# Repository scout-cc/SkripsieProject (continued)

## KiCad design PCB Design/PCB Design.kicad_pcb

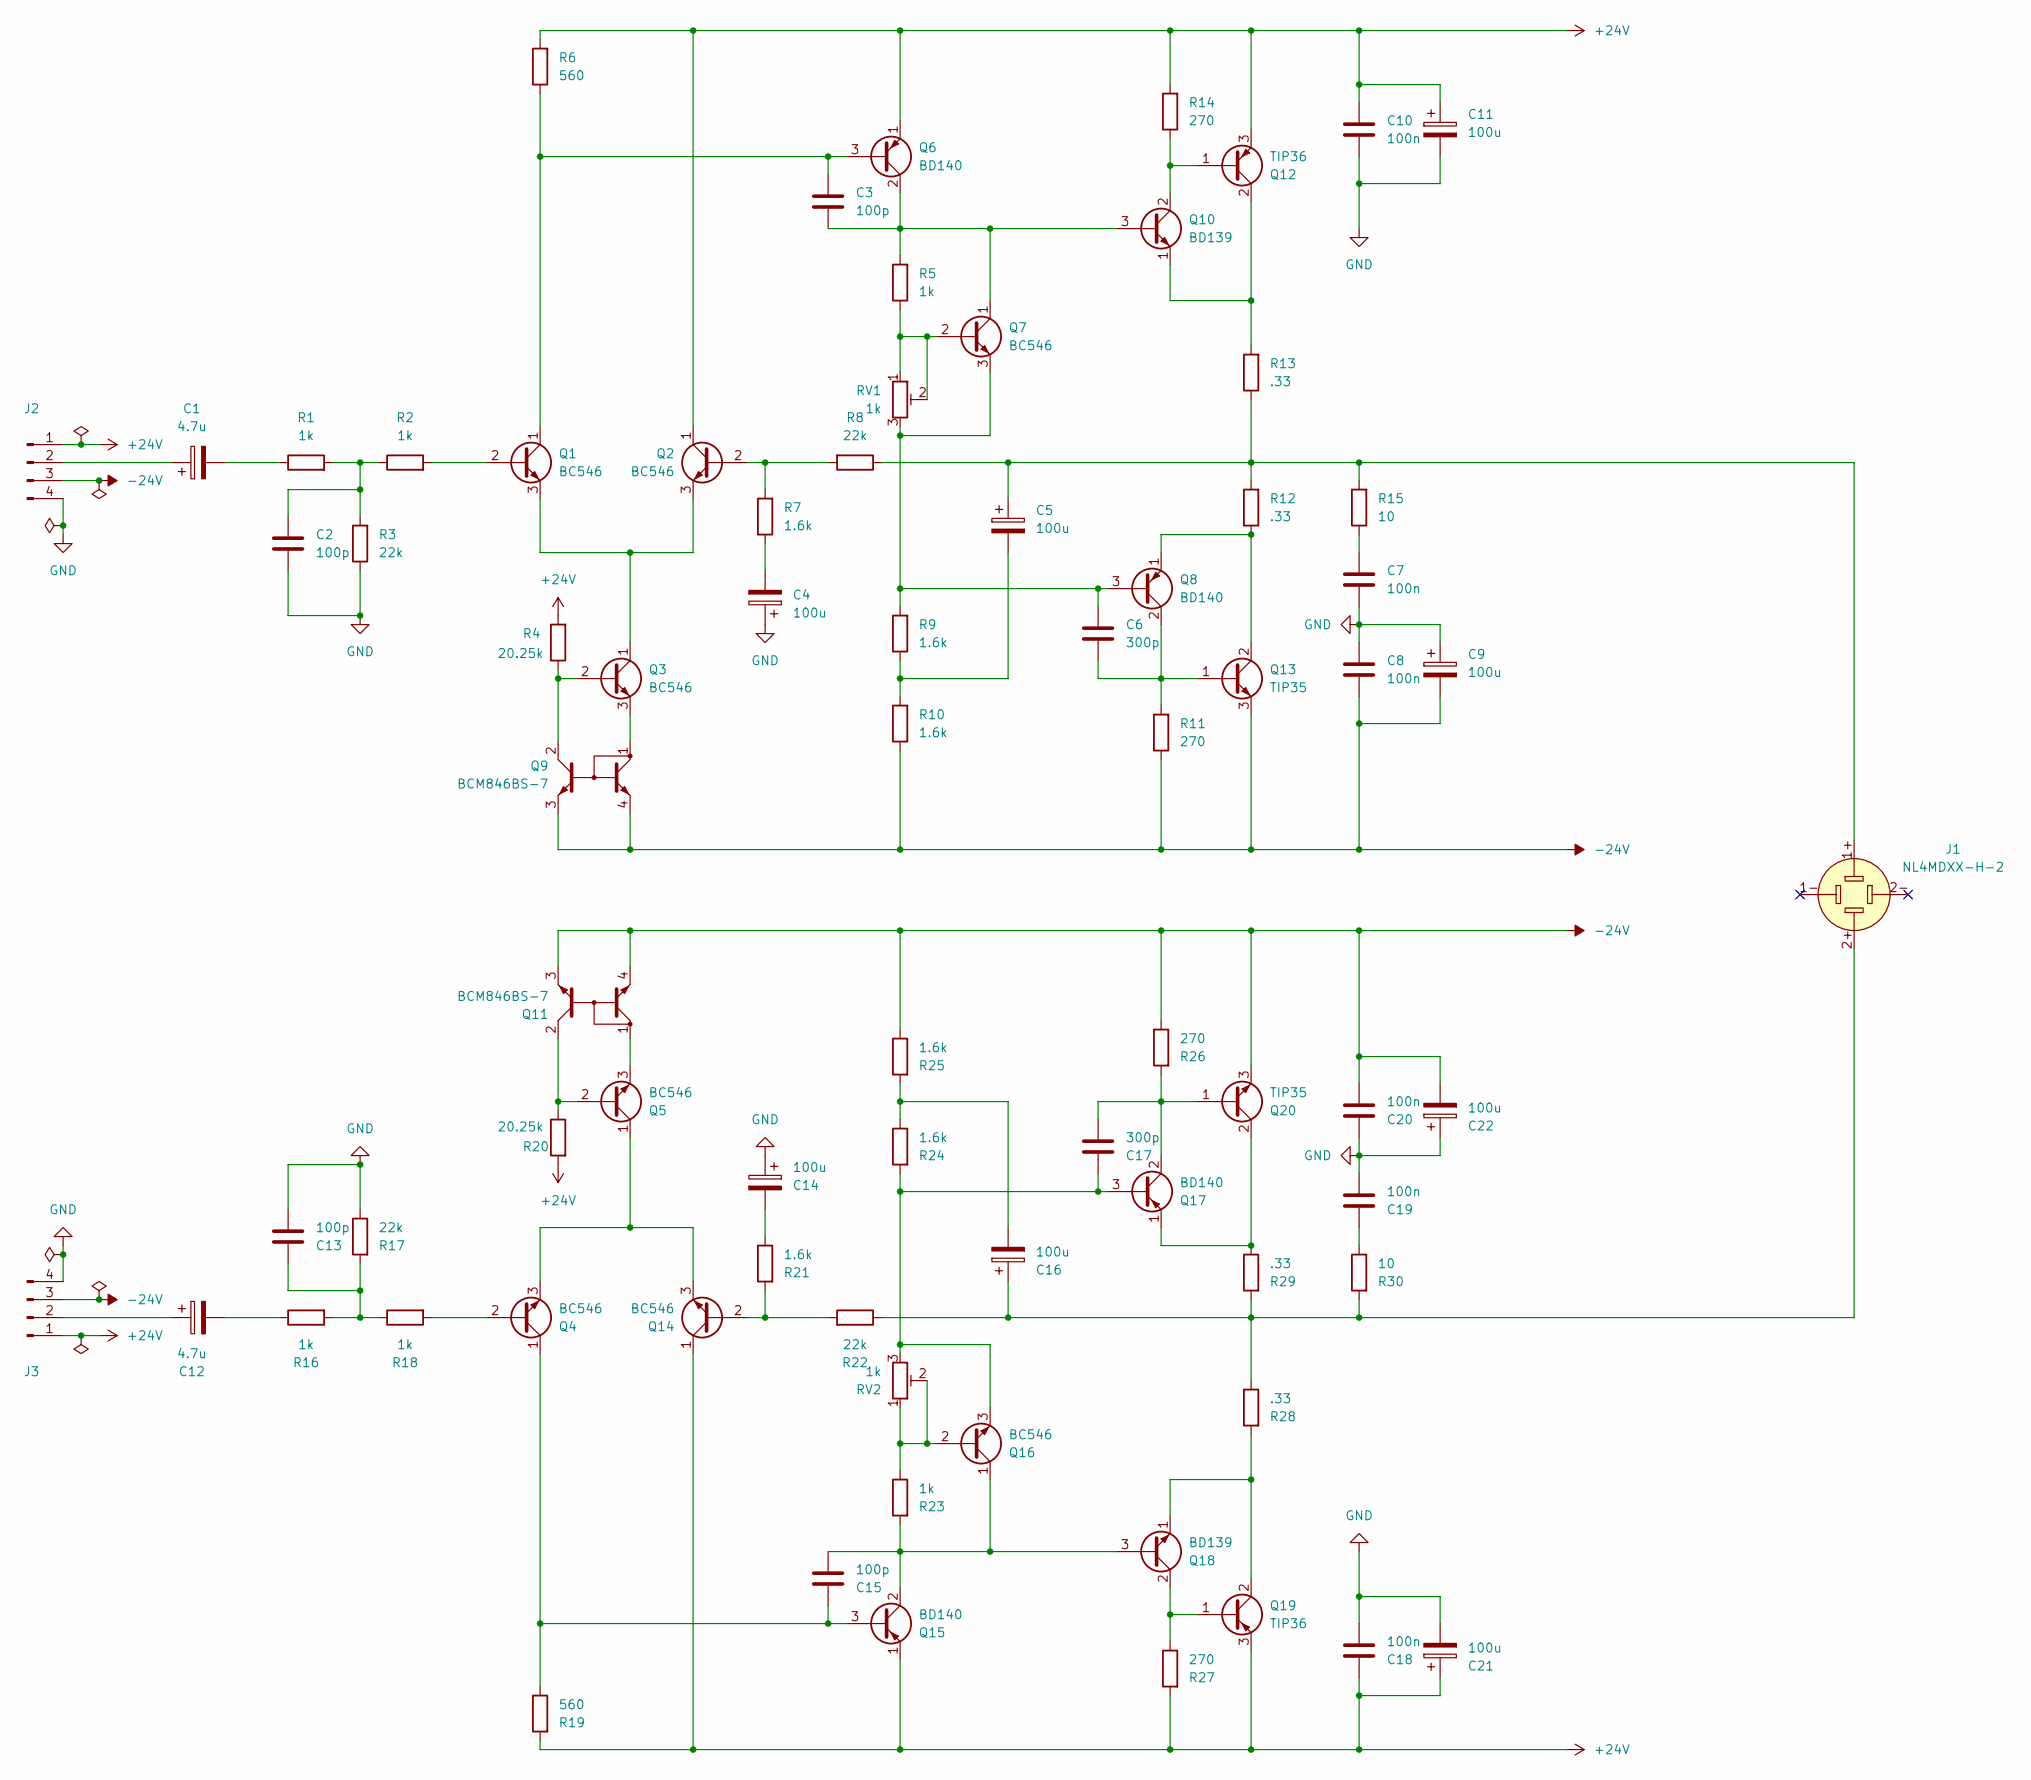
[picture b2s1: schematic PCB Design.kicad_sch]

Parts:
C1, C12: 4.7u; CP_Radial_D10.0mm_P2.50mm
C2, C3, C13, C15: 100p; C_Disc_D4.3mm_W1.9mm_P5.00mm
C4, C5, C9, C11, C14, C16, C21, C22: 100u; CP_Radial_D10.0mm_P3.50mm
C6, C17: 300p; C_Disc_D4.3mm_W1.9mm_P5.00mm
C7, C8, C10, C18, C19, C20: 100n; CP_Radial_Tantal_D5.0mm_P5.00mm
J1: NL4MDXX-H-2; Jack_speakON_Neutrik_NL4MDXX-H-2_Horizontal
J2, J3: Conn_01x04_Pin; PinHeader_1x04_P2.54mm_Vertical
Q1, Q2, Q3, Q4, Q5, Q7, Q14, Q16: BC546; TO-92_Inline
Q6, Q8, Q15, Q17: BD140; TO-126-3_Vertical
Q9, Q11: BCM846BS-7; SOT-363_SC-70-6
Q10, Q18: BD139; TO-126-3_Vertical
Q12, Q19: TIP36; TO-247-3_Horizontal_TabDown
Q13, Q20: TIP35; TO-247-3_Horizontal_TabDown
R1, R2, R5, R16, R18, R23: 1k; R_Axial_DIN0204_L3.6mm_D1.6mm_P7.62mm_Horizontal
R3, R8, R17, R22: 22k; R_Axial_DIN0204_L3.6mm_D1.6mm_P7.62mm_Horizontal
R4, R20: 20.25k; R_Axial_DIN0204_L3.6mm_D1.6mm_P7.62mm_Horizontal
R6, R19: 560; R_Axial_DIN0204_L3.6mm_D1.6mm_P7.62mm_Horizontal
R7, R21: 1.6k; R_Axial_DIN0204_L3.6mm_D1.6mm_P7.62mm_Horizontal
R9, R10, R24, R25: 1.6k; R_Axial_DIN0207_L6.3mm_D2.5mm_P10.16mm_Horizontal
R11, R14, R26, R27: 270; R_Axial_DIN0204_L3.6mm_D1.6mm_P7.62mm_Horizontal
R12, R13, R28, R29: .33; R_Axial_DIN0411_L9.9mm_D3.6mm_P20.32mm_Horizontal
R15, R30: 10; R_Axial_DIN0207_L6.3mm_D2.5mm_P10.16mm_Horizontal
RV1, RV2: 1k; Potentiometer_Bourns_3296W_Vertical

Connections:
+24V: C10.1, C11.1, C18.1, C21.1, J2.1, J3.1, Q2.1 (C), Q6.1 (E), Q12.3 (E), Q14.1 (C), Q15.1 (E), Q19.3 (E), R4.2, R6.2, R14.2, R19.2, R20.2, R27.2
-24V: C8.2, C9.2, C20.2, C22.2, J2.3, J3.3, Q9.3 (E1), Q9.4 (E2), Q11.3 (E1), Q11.4 (E2), Q13.3 (E), Q20.3 (E), R10.1, R11.1, R25.1, R26.1
GND: C2.2, C4.1, C7.2, C8.1, C9.1, C10.2, C11.2, C13.2, C14.1, C18.2, C19.2, C20.1, C21.2, C22.1, J2.4, J3.4, R3.1, R17.1
unnamed: C1.2, R1.1
unnamed: C2.1, R1.2, R2.1, R3.2
unnamed: C4.2, R7.1
unnamed: C5.1, J1.1+, R8.1, R12.2, R13.1, R15.2
unnamed: C5.2, R9.1, R10.2
unnamed: C7.1, R15.1
unnamed: C12.2, R16.1
unnamed: C13.1, R16.2, R17.2, R18.1
unnamed: C14.2, R21.1
unnamed: C16.1, J1.2+, R22.1, R28.1, R29.2, R30.2
unnamed: C16.2, R24.1, R25.2
unnamed: C19.1, R30.1
unnamed: C1.1, J2.2
unnamed: C12.1, J3.2
unnamed: Q1.2 (B), R2.2
unnamed: C3.1, Q1.1 (C), Q6.3 (B), R6.1
unnamed: Q1.3 (E), Q2.3 (E), Q3.1 (C)
unnamed: Q2.2 (B), R7.2, R8.2
unnamed: Q3.2 (B), Q9.2 (C1), R4.1
unnamed: Q3.3 (E), Q9.1 (C2)
unnamed: Q4.2 (B), R18.2
unnamed: Q7.2 (B), R5.1, RV1.1, RV1.2
unnamed: C6.1, Q7.3 (E), Q8.3 (B), R9.2, RV1.3
unnamed: C3.2, Q6.2 (C), Q7.1 (C), Q10.3 (B), R5.2
unnamed: Q10.2 (C), Q12.1 (B), R14.1
unnamed: Q10.1 (E), Q12.2 (C), R13.2
unnamed: Q5.2 (B), Q11.2 (C1), R20.1
unnamed: Q5.3 (E), Q11.1 (C2)
unnamed: C6.2, Q8.2 (C), Q13.1 (B), R11.2
unnamed: Q8.1 (E), Q13.2 (C), R12.1
unnamed: Q14.2 (B), R21.2, R22.2
unnamed: Q4.3 (E), Q5.1 (C), Q14.3 (E)
unnamed: C15.1, Q4.1 (C), Q15.3 (B), R19.1
unnamed: C15.2, Q15.2 (C), Q16.1 (C), Q18.3 (B), R23.2
unnamed: Q16.2 (B), R23.1, RV2.1, RV2.2
unnamed: C17.1, Q16.3 (E), Q17.3 (B), R24.2, RV2.3
unnamed: C17.2, Q17.2 (C), Q20.1 (B), R26.2
unnamed: Q17.1 (E), Q20.2 (C), R29.1
unnamed: Q18.2 (C), Q19.1 (B), R27.1
unnamed: Q18.1 (E), Q19.2 (C), R28.2

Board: 2 copper layers, 77 parts (0 on the bottom side), 43 nets, no tracks yet.

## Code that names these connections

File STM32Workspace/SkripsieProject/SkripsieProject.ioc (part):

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Mcu.Name=STM32G031K(4-6-8)Tx
Mcu.Package=LQFP32
Mcu.UserName=STM32G031K8Tx
PA0.GPIOParameters=GPIO_Label
PA0.GPIO_Label=Bass
PA0.Mode=IN0
PA0.Signal=ADC1_IN0
PA1.GPIOParameters=GPIO_Label
PA1.GPIO_Label=Mid
PA1.Mode=IN1
PA1.Signal=ADC1_IN1
PA13.Mode=Serial_Wire
PA13.Signal=SYS_SWDIO
PA14-BOOT0.Mode=Serial_Wire
PA14-BOOT0.Signal=SYS_SWCLK
PA4.GPIOParameters=GPIO_Label
PA4.GPIO_Label=Treble
PA4.Mode=IN4
PA4.Signal=ADC1_IN4
PA5.GPIOParameters=GPIO_Label
PA5.GPIO_Label=Volume
PA5.Mode=IN5
PA5.Signal=ADC1_IN5
PA8.GPIOParameters=GPIO_Label
PA8.GPIO_Label=Fan PWM
PA8.Signal=S_TIM1_CH1
PA9.GPIOParameters=GPIO_PuPd,GPIO_Label,GPIO_ModeDefaultEXTI
PA9.GPIO_Label=TempPulse
PA9.GPIO_ModeDefaultEXTI=GPIO_MODE_IT_RISING_FALLING
PA9.GPIO_PuPd=GPIO_NOPULL
PA9.Signal=GPXTI9
PB0.GPIOParameters=GPIO_PuPd,GPIO_Label,GPIO_ModeDefaultEXTI
PB0.GPIO_Label=Fan1 Tach
PB0.GPIO_ModeDefaultEXTI=GPIO_MODE_IT_FALLING
PB0.GPIO_PuPd=GPIO_PULLUP
PB0.Signal=GPXTI0
PB1.GPIOParameters=GPIO_PuPd,GPIO_Label,GPIO_ModeDefaultEXTI
PB1.GPIO_Label=Fan2 Tach
PB1.GPIO_ModeDefaultEXTI=GPIO_MODE_IT_FALLING
PB1.GPIO_PuPd=GPIO_PULLUP
PB1.Signal=GPXTI1
PB6.GPIOParameters=GPIO_PuPd,GPIO_Label,GPIO_ModeDefaultEXTI
PB6.GPIO_Label=Fan3 Tach
PB6.GPIO_ModeDefaultEXTI=GPIO_MODE_IT_FALLING
PB6.GPIO_PuPd=GPIO_PULLUP
PB6.Signal=GPXTI6
PB7.GPIOParameters=GPIO_PuPd,GPIO_Label,GPIO_ModeDefaultEXTI
PB7.GPIO_Label=Fan4 Tach
PB7.GPIO_ModeDefaultEXTI=GPIO_MODE_IT_FALLING
PB7.GPIO_PuPd=GPIO_PULLUP
PB7.Signal=GPXTI7
PB8.Mode=I2C
PB8.Signal=I2C1_SCL
PB9.Mode=I2C
PB9.Signal=I2C1_SDA
RCC.HSE_VALUE=8000000
RCC.SYSCLKFreq_VALUE=64000000
RCC.SYSCLKSource=RCC_SYSCLKSOURCE_PLLCLK
board=custom

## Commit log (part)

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2026-06-02 Adding intial pre git progress
2026-06-03 Power Supplies Schematic Designed
2026-06-03 Output Stage Schematic Created and complete. Next: Integrate STM32
2026-06-22 Bill of materials ETC finalised, selecting footprints next
